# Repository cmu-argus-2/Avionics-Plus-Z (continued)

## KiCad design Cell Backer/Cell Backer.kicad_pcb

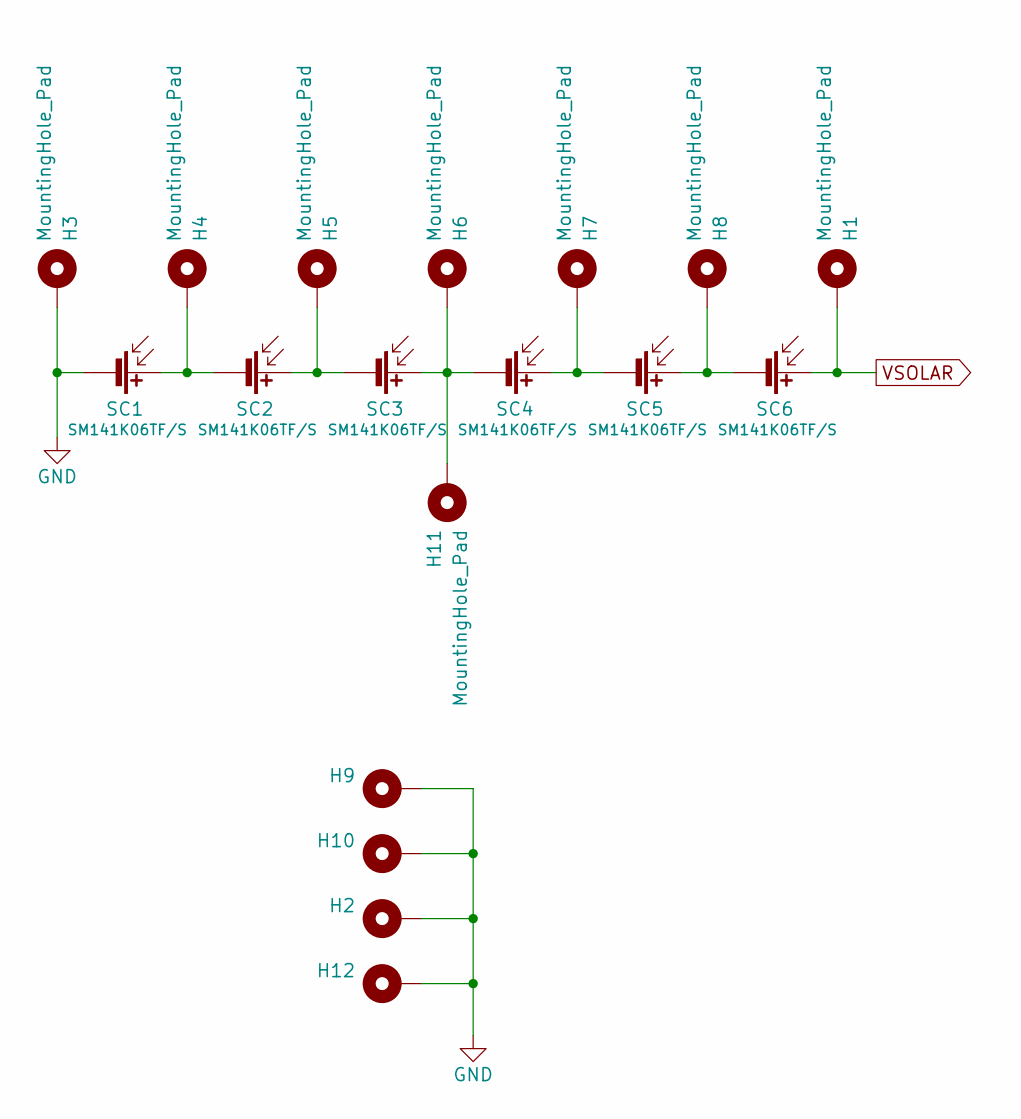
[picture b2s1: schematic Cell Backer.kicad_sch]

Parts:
H1, H2, H3, H4, H5, H6, H7, H8, H9, H10, H11, H12: MountingHole_Pad; MountingHole_1mm
SC1, SC2, SC3, SC4, SC5, SC6: SM141K06TF/S; SM141K06TF_S

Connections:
GND: H2.1, H3.1, H9.1, H10.1, H12.1, SC1.2 (-)
unnamed: H4.1, SC1.1 (+), SC2.2 (-)
unnamed: H5.1, SC2.1 (+), SC3.2 (-)
unnamed: H6.1, H11.1, SC3.1 (+), SC4.2 (-)
unnamed: H7.1, SC4.1 (+), SC5.2 (-)
unnamed: H8.1, SC5.1 (+), SC6.2 (-)
VSOLAR: H1.1, SC6.1 (+)

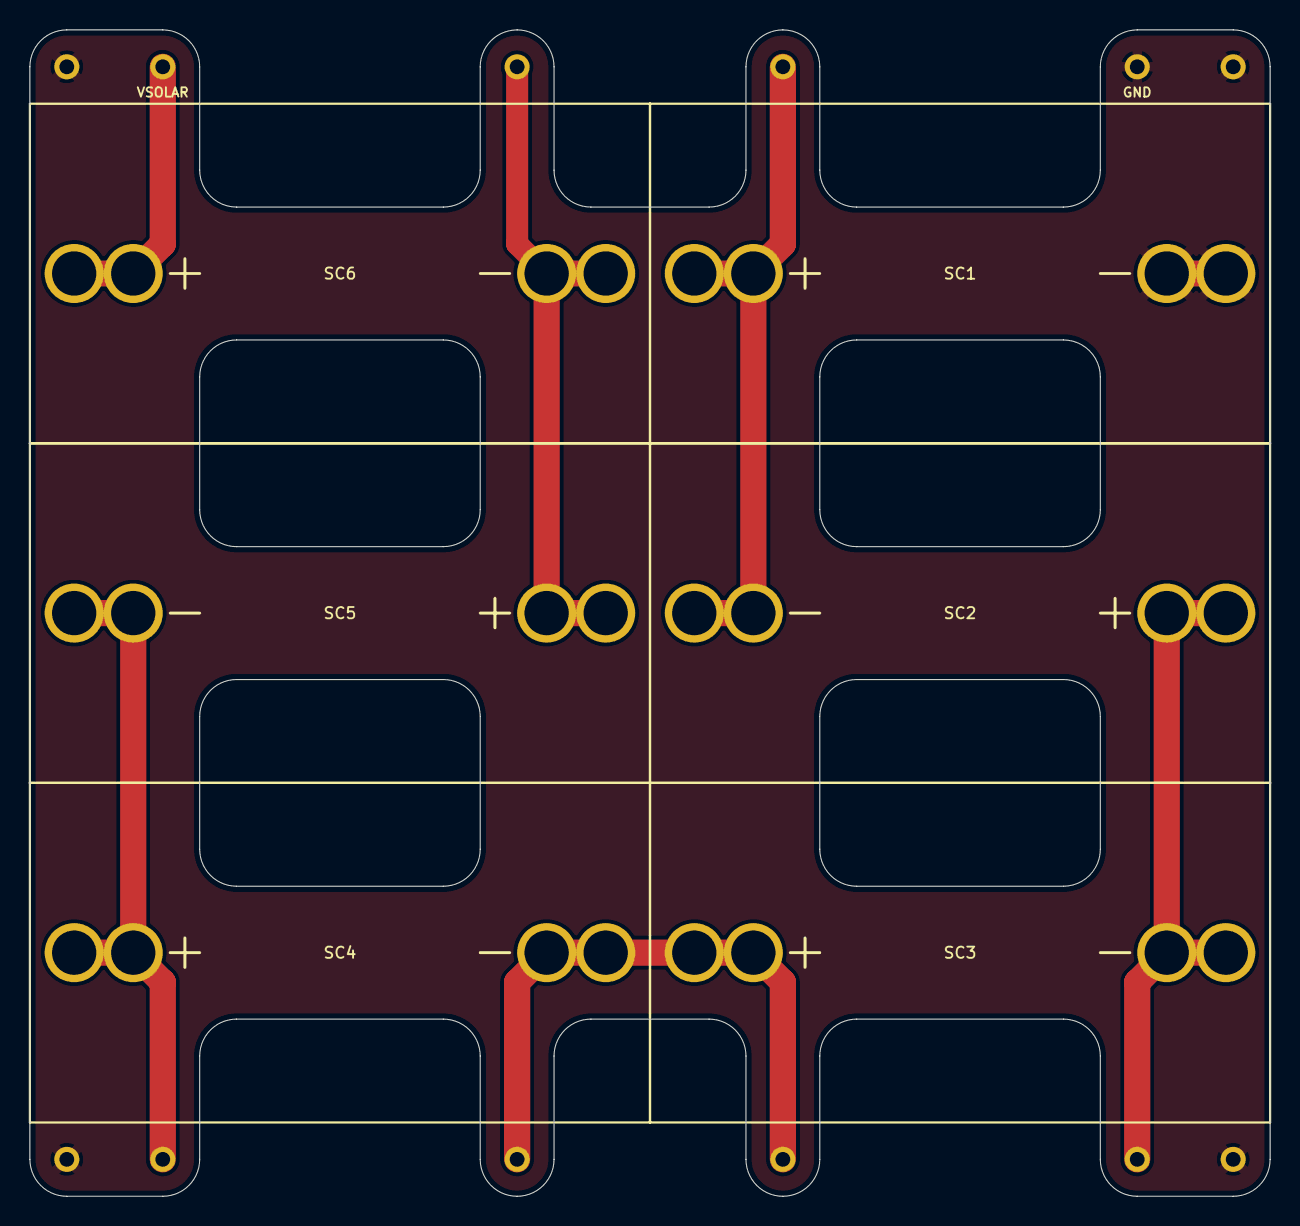
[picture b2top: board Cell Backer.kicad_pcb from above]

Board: 2 copper layers, 84.0 x 79.0 mm, 18 parts (0 on the bottom side), 7 nets.

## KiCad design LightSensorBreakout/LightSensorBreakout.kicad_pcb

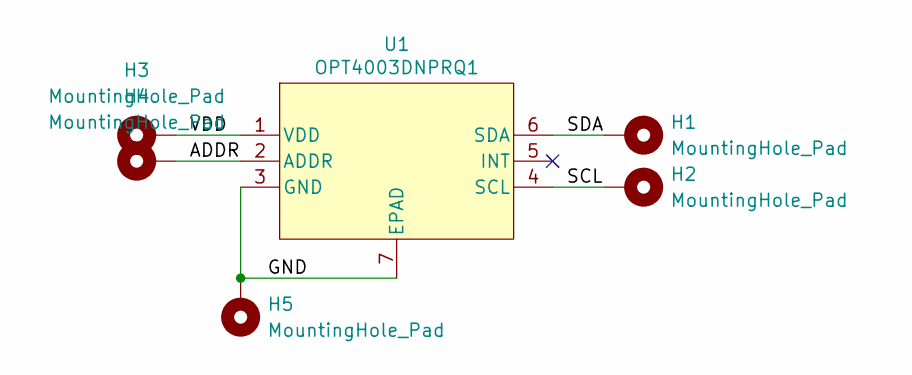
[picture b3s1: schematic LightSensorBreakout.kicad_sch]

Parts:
H1, H2, H3, H4, H5: MountingHole_Pad; LightSensorPad
U1: OPT4003DNPRQ1; OPT4003

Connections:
/ADDR: H4.1, U1.2 (ADDR)
/GND: H5.1, U1.3 (GND), U1.7 (EPAD)
/SCL: H2.1, U1.4 (SCL)
/SDA: H1.1, U1.6 (SDA)
/VDD: H3.1, U1.1 (VDD)

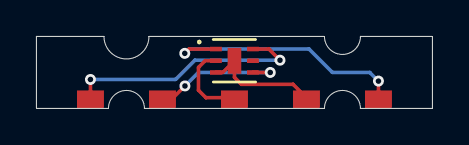
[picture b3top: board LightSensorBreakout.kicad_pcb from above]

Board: 2 copper layers, 22.0 x 4.0 mm, 6 parts (0 on the bottom side), 5 nets.

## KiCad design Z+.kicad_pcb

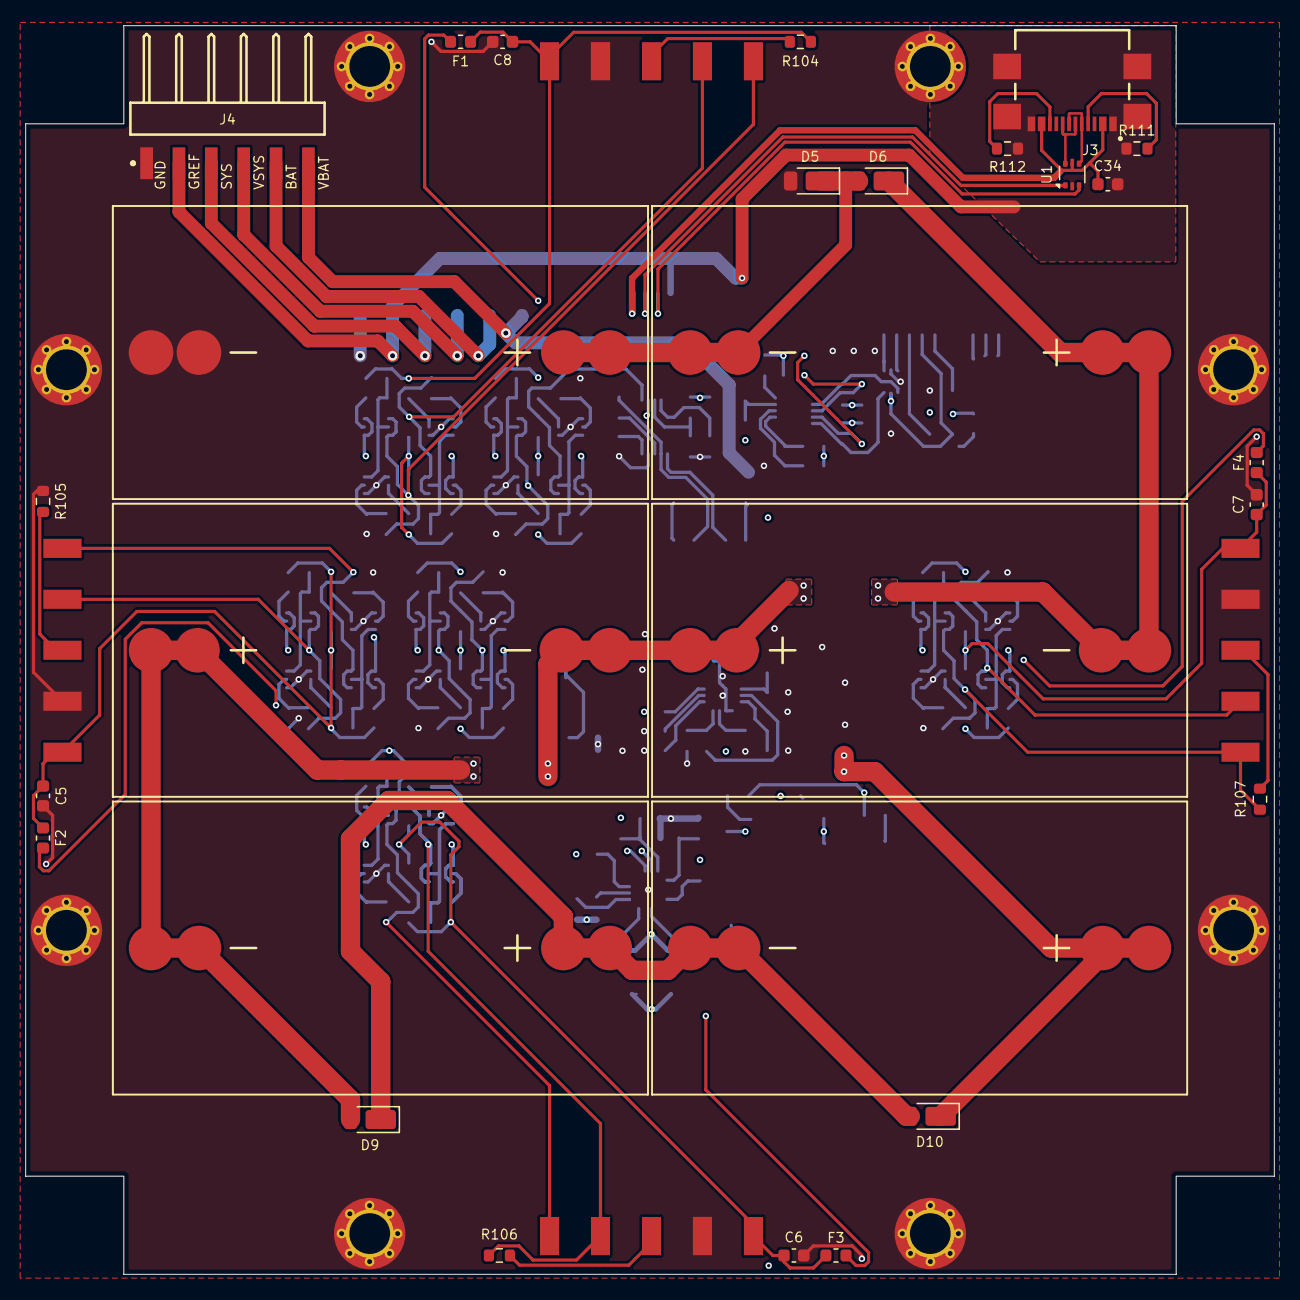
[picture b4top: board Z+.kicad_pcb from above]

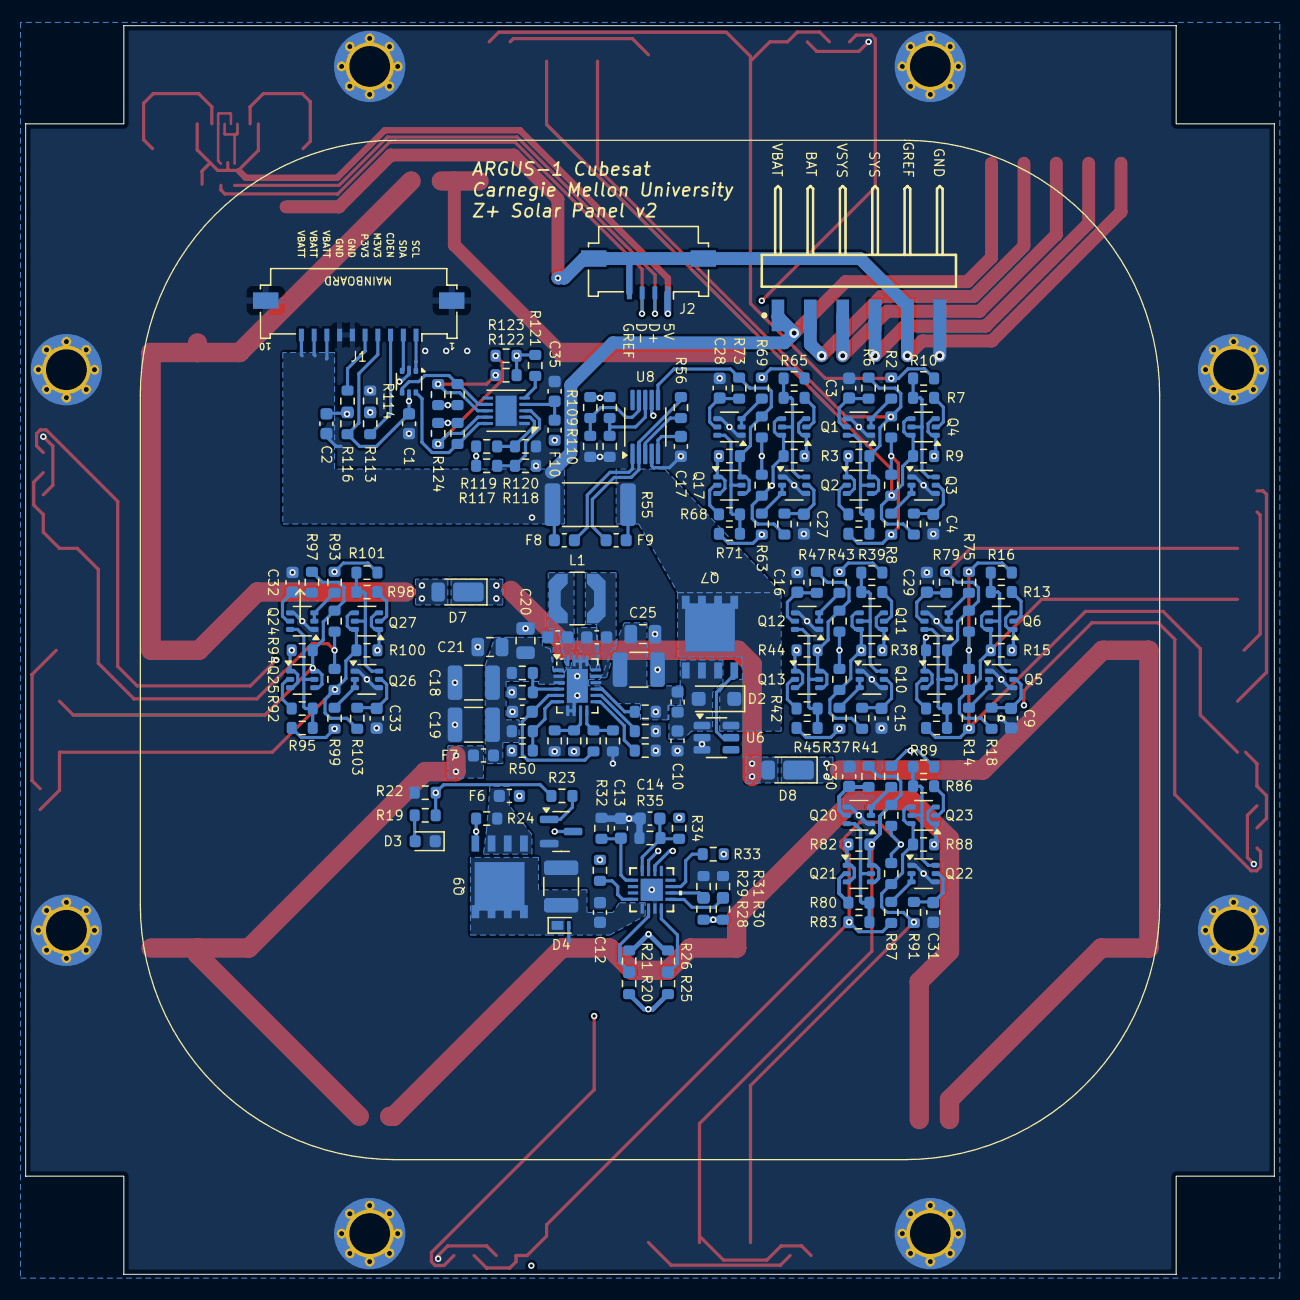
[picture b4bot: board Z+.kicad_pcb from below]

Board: 4 copper layers, 98.0 x 98.0 mm, 239 parts (199 on the bottom side), 141 nets.

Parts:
C1, C2, C5, C6, C7, C8: 100nF; C_0603_1608Metric
C3, C4, C9, C15, C16, C27, C28, C29, C30, C31, C32, C33: 10nF; C_0603_1608Metric
C10, C12, C14, C35: 0.1uF; C_0603_1608Metric
C11, C19: 10uF; C_1210_3225Metric
C13: 1nF; C_0603_1608Metric
C17: 3.3nF; C_0603_1608Metric
C18, C26: 47uF; C_1210_3225Metric
C20, C21, C25: 1uF; C_0805_2012Metric
C22, C23: 22nF; C_0603_1608Metric
C24: 4.7uF; C_0603_1608Metric
C34: 4u7; C_0603_1608Metric
D2: PMEG4005EH; D_SOD-123F
D3: GREEN; LED_0603_1608Metric
D4: 10V; Nexperia_DSN1608-2_1.6x0.8mm
D5, D6, D7, D8, D9, D10: DFLS130L-7; D_PowerDI-123
F1, F2, F3, F4: Fuse_Small; Fuse_0603_1608Metric
F5, F6: 500mA; Fuse_0603_1608Metric
F7, F8, F9, F10: 100mA; Fuse_0603_1608Metric
H1, H2, H3, H4, H5, H6, H7, H8: MountingHole_Pad; MountingHole_3.2mm_M3_DIN965_Pad_TopBottom
J1: 200528-0100; Molex_200528-0100_1x10-1MP_P1.00mm_Horizontal
J2: Conn_01x04_MountingPin; Molex_200528-0040_1x04-1MP_P1.00mm_Horizontal
J3: USB4110GFA; GCT_USB4110GFA
J4, J5: BG301-06-X-XXXX-X-X_REVC; GCT_BG301-06-X-XXXX-X-X_REVC
L1: 6.8uH; L_Coilcraft_LPS4018
Q1, Q3, Q5, Q10, Q12, Q14, Q16, Q18, Q20, Q22, Q24, Q26: NX3008NBKS; SOT-363_SC-70-6
Q2, Q4, Q6, Q11, Q13, Q15, Q17, Q19, Q21, Q23, Q25, Q27: MBT2222ADW1T1; SOT-363_SC-70-6
Q7, Q9: SiRA99DP; PowerPAK SO-8
Q8: IRLML2803; SOT-23
R1, R7, R13, R36, R42, R62, R68, R74, R80, R86, R92, R98: 680R; R_0603_1608Metric
R2, R8, R14, R37, R43, R52, R63, R69, R75, R81, R87, R93, R99: 100K; R_0603_1608Metric
R3, R9, R15, R38, R44, R64, R70, R76, R82, R88, R94, R100: DNI (0R); R_0603_1608Metric
R4, R5, R10, R11, R16, R17, R39, R40, R45, R46, R65, R66, R71, R72, R77, R78, R83, R84, R89, R90, R95, R96, R101, R102, R121, R122, R123: 10K; R_0603_1608Metric
R6, R12, R18, R41, R47, R54, R67, R73, R79, R85, R91, R97, R103: 200K; R_0603_1608Metric
R19: 2.7k; R_0603_1608Metric
R20, R21, R25, R26, R28, R29, R30, R31, R57, R59, R60, R61, R104, R105, R106, R107, R108, R109, R110, R113, R114, R115, R116, R124, R125: 0R; R_0603_1608Metric
R22, R24, R27: 10k; R_0603_1608Metric
R23: 4k7; R_0603_1608Metric
R32, R34, R35: TBD; R_0603_1608Metric
R33: 1k; R_0603_1608Metric
R48, R49: 1.91M; R_0603_1608Metric
R50: 126k; R_0603_1608Metric
R51: 182k; R_0603_1608Metric
R53: 1.47M; R_0603_1608Metric
R55: ?R; R_2512_6332Metric
R56: 1K; R_0603_1608Metric
R58, R126, R127: 0R (DNI); R_0603_1608Metric
R111, R112: 5k1; R_0603_1608Metric
R117, R118, R119, R120: ?; R_0603_1608Metric
SC1, SC2, SC3, SC4, SC5, SC6: SM141K06L; SM141K06TF
U1, U10: USBLC6-2P6; SOT-666
U2, U3, U4, U5: SunSensor
U6: LTC4412xS6; TSOT-23-6
U7: DRV8235RTER; WQFN16_RTE_TEX
U8: ADM1176-1ARMZ-R7; MSOP-10_3x3mm_P0.5mm
U9: LTC3130; QFN-20-1EP_3x4mm_P0.5mm_EP1.65x2.65mm
U11: LTC4316xDD; DFN-10-1EP_3x3mm_P0.5mm_EP1.65x2.38mm

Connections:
/Coil Driver/A0_COIL: R28.1, R29.2, U7.10 (A0)
/Coil Driver/A1_COIL: R30.1, R31.2, U7.9 (A1)
/Coil Driver/IPROPI: C13.1, R32.1, U7.1 (IPROPI)
/Coil Driver/SCL_M: Q11.4 (E2), Q11.6 (C1), R38.1, R40.2, R41.1, U7.15 (SCL)
/Coil Driver/SDA_M: Q13.4 (E2), Q13.6 (C1), R44.1, R46.2, R47.1, U7.14 (SDA)
/Coil Driver/VM: C11.1, C12.1, D4.1 (K), Q9.2 (D), U7.5 (VM)
/Coil Driver/VREF: C14.1, R34.2, R35.1, U7.16 (VREF)
/Coil Driver/coil: R20.2, R21.1, R25.2, R26.1
/I2C Translator/SCLOUT: R123.1, R124.2, U11.9 (SCLOUT)
/I2C Translator/SDAOUT: R122.1, R125.2, U11.8 (SDAOUT)
/Interfaces/Mainboard FPC/COIL_DRIVER_EN_OR_MAIN_3V3: J1.3, R113.1
/Interfaces/Mainboard FPC/PERI_3V3_OR_GND: J1.5, R115.1
/Interfaces/RBF/BATT: J4.5, J5.2
/Interfaces/RBF/SYS: J4.3, J5.4
/Interfaces/RBF/VSYS: J4.4, J5.3
/Interfaces/USB-C/CC1: J3.A5 (CC1), R111.2
/Interfaces/USB-C/CC2: J3.B5 (CC2), R112.2
/Interfaces/USB-C/D+: J3.A6 (DP1), J3.B6 (DP2), U1.6 (I/O1)
/Interfaces/USB-C/D-: J3.A7 (DN1), J3.B7 (DN2), U1.4 (I/O2)
/Interfaces/USB-C/D_CONN+: J2.2, U1.1 (I/O1)
/Interfaces/USB-C/D_CONN-: J2.3, U1.3 (I/O2)
/Solar Charger/A0_S: R57.1, R108.2, U8.8 (A0)
/Solar Charger/A1_S: R109.1, R110.2, U8.9 (A1)
/Solar Charger/Charge OR-ing2/IN: C25.1, C26.1, F5.2, R52.2, R53.1, U9.14 (VOUT)
/Solar Charger/MPPT2/FB: R53.2, R54.1, U9.9 (FB)
/Solar Charger/MPPT2/MPPC: R49.2, R50.1, U9.6 (MPPC)
/Solar Charger/MPPT2/RUN: R48.2, R51.1, U9.4 (RUN)
/Solar Charger/MPPT2/VCC: C24.1, R58.2, U9.5 (VCC)
/Solar Charger/MPPT2/VIN: C18.1, C19.1, C20.1, C21.1, F7.1, R48.1, R49.1, U9.2 (PVIN), U9.3 (VIN)
/Solar Charger/PGOOD3: R52.1, U9.13 (PGOOD)
/Sun Pyramid/LS0_3V3: C8.1, F1.2, R2.1, R4.1, R5.1, R8.1, R10.1, R11.1, R104.2, U2.1 (3.3V)
/Sun Pyramid/LS0_ADDR: R104.1, U2.3 (ADDR)
/Sun Pyramid/LS0_SCL: Q2.4 (E2), Q2.6 (C1), R3.1, R5.2, R6.1, U2.4 (SCL)
/Sun Pyramid/LS0_SDA: Q4.4 (E2), Q4.6 (C1), R9.1, R11.2, R12.1, U2.5 (SDA)
/Sun Pyramid/LS1_3V3: C5.1, F2.2, R14.1, R16.1, R17.1, R75.1, R77.1, R78.1, U3.1 (3.3V)
/Sun Pyramid/LS1_ADDR: R105.1, U3.3 (ADDR)
/Sun Pyramid/LS1_SCL: Q6.4 (E2), Q6.6 (C1), R15.1, R17.2, R18.1, U3.4 (SCL)
/Sun Pyramid/LS1_SDA: Q19.4 (E2), Q19.6 (C1), R76.1, R78.2, R79.1, U3.5 (SDA)
/Sun Pyramid/LS2_3V3: C6.1, F3.2, R81.1, R83.1, R84.1, R87.1, R89.1, R90.1, U4.1 (3.3V)
/Sun Pyramid/LS2_ADDR: R106.1, U4.3 (ADDR)
/Sun Pyramid/LS2_SCL: Q21.4 (E2), Q21.6 (C1), R82.1, R84.2, R85.1, R106.2, U4.4 (SCL)
/Sun Pyramid/LS2_SDA: Q23.4 (E2), Q23.6 (C1), R88.1, R90.2, R91.1, U4.5 (SDA)
/Sun Pyramid/LS3_3V3: C7.1, F4.2, R93.1, R95.1, R96.1, R99.1, R101.1, R102.1, U5.1 (3.3V)
/Sun Pyramid/LS3_ADDR: R107.1, U5.3 (ADDR)
/Sun Pyramid/LS3_SCL: Q25.4 (E2), Q25.6 (C1), R94.1, R96.2, R97.1, U5.4 (SCL)
/Sun Pyramid/LS3_SDA: Q27.4 (E2), Q27.6 (C1), R100.1, R102.2, R103.1, R107.2, U5.5 (SDA)
COIL_DRIVER_EN: R19.1, R22.2, R23.1, R113.2, R114.2
COIL_N: R25.1, R26.2, U7.8 (OUT2)
COIL_P: R20.1, R21.2, U7.6 (OUT1)
GND: C1.2, C2.2, C3.2, C4.2, C5.2, C6.2, C7.2, C8.2, C9.2, C10.2, C11.2, C12.2, C13.2, C14.2, C15.2, C16.2, C17.1, C18.2, C19.2, C20.2, C21.2, C24.2, C25.2, C26.2, C27.2, C28.2, C29.2, C30.2, C31.2, C32.2, C33.2, C35.2, D3.1 (K), D4.2 (A), D5.2 (A), H1.1, H2.1, H3.1, H4.1, H5.1, H6.1, H7.1, H8.1, J1.6, J1.7, J1.MP (MountPin), J4.1, J5.6, Q1.1 (S2), Q1.4 (S1), Q3.1 (S2), Q3.4 (S1), Q5.1 (S2), Q5.4 (S1), Q8.2 (S), Q10.1 (S2), Q10.4 (S1), Q12.1 (S2), Q12.4 (S1), Q14.1 (S2), Q14.4 (S1), Q16.1 (S2), Q16.4 (S1), Q18.1 (S2), Q18.4 (S1), Q20.1 (S2), Q20.4 (S1), Q22.1 (S2), Q22.4 (S1), Q24.1 (S2), Q24.4 (S1), Q26.1 (S2), Q26.4 (S1), R22.1, R29.1, R31.1, R32.2, R35.2, R50.2, R51.2, R54.2, R59.2, R60.2, R61.1, R105.2, R108.1, R110.1, R114.1, R118.1, R120.1, SC1.2 (-), U2.2 (GND), U3.2 (GND), U4.2 (GND), U5.2 (GND), U6.2 (GND), U6.3 (CTL), U7.7 (GND), U7.17 (EPAD), U8.4 (GND), U9.7 (GND), U9.8 (GND), U9.17 (GND), U9.18 (PGND), U9.19 (PGND), U9.21 (GND), U10.2 (GND), U11.1 (GND), U11.11 (EP)
GNDREF: C34.2, J2.4, J2.MP (MountPin), J3.A1/B12 (GND), J3.B1/A12 (GND), J3.S1 (GND), J3.S2 (GND), J3.S3 (GND), J3.S4 (GND), J4.2, J5.5, R111.1, R112.1, U1.2 (GND)
MAIN_3V3: C1.1, J1.4, R27.1, R28.2, R30.2, R33.2, R34.1, R37.1, R39.1, R40.1, R43.1, R45.1, R46.1, R57.2, R63.1, R65.1, R66.1, R69.1, R71.1, R72.1, R109.2, R116.1, U10.5 (VBUS)
unnamed: C10.1, D2.2 (A), F5.1, Q7.3 (S), U6.1 (VIN)
unnamed: D3.2 (A), R19.2
unnamed: D5.1 (K), D6.2 (A), SC1.1 (+), SC2.2 (-)
unnamed: D6.1 (K), D7.2 (A), SC2.1 (+), SC3.2 (-)
unnamed: D7.1 (K), D8.2 (A), SC3.1 (+), SC4.2 (-)
unnamed: D8.1 (K), D9.2 (A), SC4.1 (+), SC5.2 (-)
unnamed: D9.1 (K), D10.2 (A), SC5.1 (+), SC6.2 (-)
unnamed: J1.1, U10.1 (I/O1)
unnamed: J1.2, U10.3 (I/O2)
unnamed: Q1.6 (D1), Q2.5 (B2), R1.2, R4.2
unnamed: Q1.2 (G2), Q1.3 (D2), R2.2
unnamed: C3.1, Q1.5 (G1), R6.2
unnamed: Q2.2 (B1), R1.1
unnamed: Q3.6 (D1), Q4.5 (B2), R7.2, R10.2
unnamed: Q3.2 (G2), Q3.3 (D2), R8.2
unnamed: C4.1, Q3.5 (G1), R12.2
unnamed: Q4.2 (B1), R7.1
unnamed: Q5.6 (D1), Q6.5 (B2), R13.2, R16.2
unnamed: Q5.2 (G2), Q5.3 (D2), R14.2
unnamed: C9.1, Q5.5 (G1), R18.2
unnamed: Q6.2 (B1), R13.1
unnamed: Q7.1 (G), U6.5 (GATE)
unnamed: Q8.3 (D), Q9.1 (G), R24.1
unnamed: Q8.1 (G), R23.2
unnamed: F6.1, Q9.3 (S), R24.2
unnamed: Q10.6 (D1), Q11.5 (B2), R36.2, R39.2
unnamed: Q10.2 (G2), Q10.3 (D2), R37.2
unnamed: C15.1, Q10.5 (G1), R41.2
unnamed: Q11.2 (B1), R36.1
unnamed: Q12.6 (D1), Q13.5 (B2), R42.2, R45.2
unnamed: Q12.2 (G2), Q12.3 (D2), R43.2
unnamed: C16.1, Q12.5 (G1), R47.2
unnamed: Q13.2 (B1), R42.1
unnamed: Q14.6 (D1), Q15.5 (B2), R62.2, R65.2
unnamed: Q14.2 (G2), Q14.3 (D2), R63.2
unnamed: C27.1, Q14.5 (G1), R67.2
unnamed: Q15.2 (B1), R62.1
unnamed: Q16.6 (D1), Q17.5 (B2), R68.2, R71.2
unnamed: Q16.2 (G2), Q16.3 (D2), R69.2
unnamed: C28.1, Q16.5 (G1), R73.2
unnamed: Q17.2 (B1), R68.1
unnamed: Q18.6 (D1), Q19.5 (B2), R74.2, R77.2
unnamed: Q18.2 (G2), Q18.3 (D2), R75.2
unnamed: C29.1, Q18.5 (G1), R79.2
unnamed: Q19.2 (B1), R74.1
unnamed: Q20.6 (D1), Q21.5 (B2), R80.2, R83.2
unnamed: Q20.2 (G2), Q20.3 (D2), R81.2
unnamed: C30.1, Q20.5 (G1), R85.2
unnamed: Q21.2 (B1), R80.1
unnamed: Q22.6 (D1), Q23.5 (B2), R86.2, R89.2
unnamed: Q22.2 (G2), Q22.3 (D2), R87.2
unnamed: C31.1, Q22.5 (G1), R91.2
unnamed: Q23.2 (B1), R86.1
unnamed: Q24.6 (D1), Q25.5 (B2), R92.2, R95.2
unnamed: Q24.2 (G2), Q24.3 (D2), R93.2
unnamed: C32.1, Q24.5 (G1), R97.2
unnamed: Q25.2 (B1), R92.1
unnamed: Q26.6 (D1), Q27.5 (B2), R98.2, R101.2
unnamed: Q26.2 (G2), Q26.3 (D2), R99.2
unnamed: C33.1, Q26.5 (G1), R103.2
unnamed: Q27.2 (B1), R98.1
unnamed: R27.2, U7.4 (NFAULT)
unnamed: R33.1, U7.11 (NSLEEP)
unnamed: R56.2, U8.3 (ON)
unnamed: F9.1, R56.1, U8.2 (SENSE)
unnamed: C17.2, U8.5 (TIMER)
unnamed: F8.1, U8.1 (VCC)
unnamed: C22.2, U9.1 (BST1)
unnamed: C23.1, U9.16 (BST2)
unnamed: R61.2, U9.12 (EXTVCC)
unnamed: R58.1, R59.1, U9.10 (ILIM)
unnamed: R60.1, U9.11 (MODE)
unnamed: C22.1, L1.1, U9.20 (SW1)
unnamed: C23.2, L1.2, U9.15 (SW2)
unnamed: R121.1, U11.5 (ENABLE)
unnamed: C35.1, F10.2, U11.4 (V_{CC})
unnamed: R119.1, R120.2, U11.2 (XORH)
unnamed: R117.1, R118.2, U11.3 (XORL)
PERI_3V3: C2.1, F1.1, F2.1, F3.1, F4.1, F10.1, R115.2, R116.2, R117.2, R119.2, R121.2, R122.2, R123.2
SCL: Q2.1 (E1), Q2.3 (C2), Q6.1 (E1), Q6.3 (C2), Q11.1 (E1), Q11.3 (C2), Q17.1 (E1), Q17.3 (C2), Q21.1 (E1), Q21.3 (C2), Q25.1 (E1), Q25.3 (C2), R3.2, R15.2, R38.2, R70.2, R82.2, R94.2, R124.1, R126.1
SCL_MB: R126.2, U10.6 (I/O1), U11.10 (SCLIN)
SCL_SPWR: Q17.4 (E2), Q17.6 (C1), R70.1, R72.2, R73.1, U8.6 (SCL)
SDA: Q4.1 (E1), Q4.3 (C2), Q13.1 (E1), Q13.3 (C2), Q15.1 (E1), Q15.3 (C2), Q19.1 (E1), Q19.3 (C2), Q23.1 (E1), Q23.3 (C2), Q27.1 (E1), Q27.3 (C2), R9.2, R44.2, R64.2, R76.2, R88.2, R100.2, R125.1, R127.1
SDA_MB: R127.2, U10.4 (I/O2), U11.7 (SDAIN)
SDA_SPWR: Q15.4 (E2), Q15.6 (C1), R64.1, R66.2, R67.1, U8.7 (SDA)
USB_5V: C34.1, J2.1, J3.A4/B9 (VBUS), J3.B4/A9 (VBUS), U1.5 (VBUS)
VBATT: F6.2, F8.2, J1.8, J1.9, J1.10, J4.6, J5.1, R55.2
VCHRG: D2.1 (K), F9.2, Q7.2 (D), R55.1, U6.6 (SENSE)
VSOLAR: D10.1 (K), F7.2, SC6.1 (+)

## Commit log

2025-02-10 Fixed Z+ structure
2025-02-16 Cleaned up silkscreen
2025-02-17 Added BOM
2025-02-28 Added gerbers
2025-06-17 v3.1 Updates
2025-06-19 Re-Exported BOM
2026-01-21 Local Stash
2026-02-09 V4 Updates
2026-03-23 Coil direction comment clarification
